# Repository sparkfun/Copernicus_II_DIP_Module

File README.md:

Copernicus II DIP Module
========================

[

[*Copernicus II DIP Module (GPS-11858)*](https://www.sparkfun.com/products/11858)

This breakout board allows access to the SMD pins of the Copernicus II GPS module from Trimble. 

Repository Contents
-------------------
* **/Hardware** - All Eagle design files (.brd, .sch)
* **/Libraries** - All Arduino libraries and board examples
* **/Production** - Test bed files and production panel files

Documentation
-------------------
* **[Hookup Guide](https://learn.sparkfun.com/tutorials/copernicus-ii-hookup-guide)** - Basic hookup guide

Version History
---------------
* [GPS-11067 - v13](https://github.com/sparkfun/Copernicus_II_DIP_Module/tree/79d04dc032e8ecc2a1069bf3677cde6e07c77bf1)

License Information
-------------------
The hardware is released under [Creative Commons Share-alike 3.0](http://creativecommons.org/licenses/by-sa/3.0/). 
All other code is open source so please feel free to do anything you want with it; you buy me a beer if you use this and we meet someday ([Beerware license](http://en.wikipedia.org/wiki/Beerware)).

The library was written by @trbabb. The original repository can be found [here](https://github.com/trbabb/copernicus).

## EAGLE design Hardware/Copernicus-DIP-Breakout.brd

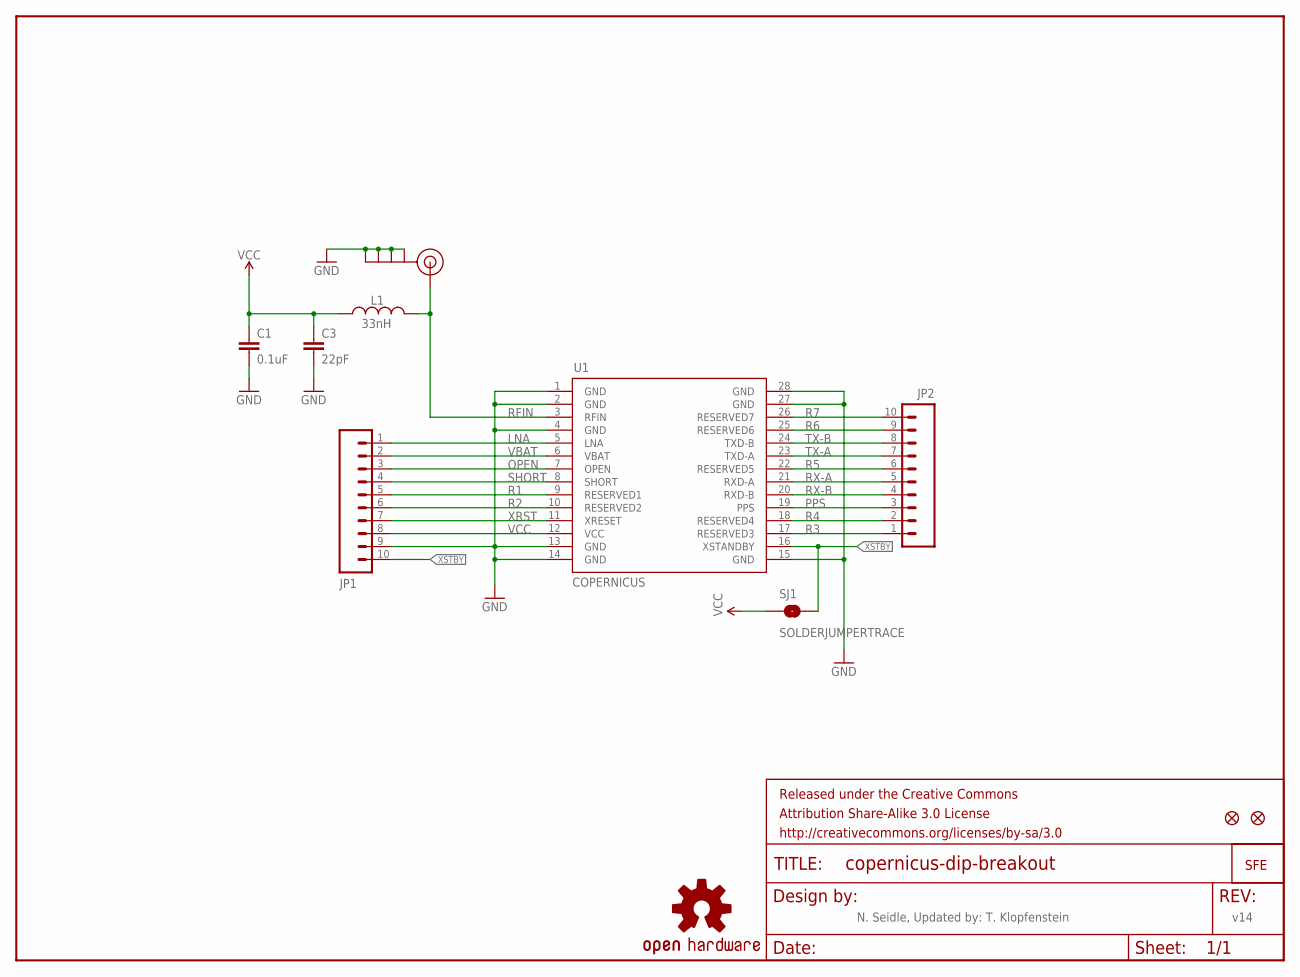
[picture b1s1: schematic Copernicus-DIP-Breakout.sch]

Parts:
C1: 0.1uF; 0603-CAP
C3: 22pF; 0603-CAP
FRAME1: FRAME-LETTER; CREATIVE_COMMONS
JP1, JP2: M10"; 1X10
JP3: SMA_EDGE
JP4: LOGO-SFESK; SFE-LOGO-FLAME
L1: 33nH; 0603
SJ1: SOLDERJUMPERTRACE; SJ_2S-TRACE
U1: COPERNICUS
U$1: OSHW-LOGOS; OSHW-LOGO-S
U$2, U$3: FIDUCIAL1X2; FIDUCIAL-1X2

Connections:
GND: C1.2, C3.2, JP1.9, JP3.GND@0 (GND), JP3.GND@1 (GND), JP3.GND@2 (GND), JP3.GND@3 (GND), U1.1 (GND), U1.2 (GND), U1.4 (GND), U1.13 (GND), U1.14 (GND), U1.15 (GND), U1.27 (GND), U1.28 (GND)
LNA: JP1.1, U1.5 (LNA)
OPEN: JP1.3, U1.7 (OPEN)
PPS: JP2.3, U1.19 (PPS)
R1: JP1.5, U1.9 (RESERVED1)
R2: JP1.6, U1.10 (RESERVED2)
R3: JP2.1, U1.17 (RESERVED3)
R4: JP2.2, U1.18 (RESERVED4)
R5: JP2.6, U1.22 (RESERVED5)
R6: JP2.9, U1.25 (RESERVED6)
R7: JP2.10, U1.26 (RESERVED7)
RFIN: JP3.SIG (SIGNAL), L1.2, U1.3 (RFIN)
RX-A: JP2.5, U1.21 (RXD-A)
RX-B: JP2.4, U1.20 (RXD-B)
SHORT: JP1.4, U1.8 (SHORT)
TX-A: JP2.7, U1.23 (TXD-A)
TX-B: JP2.8, U1.24 (TXD-B)
VBAT: JP1.2, U1.6 (VBAT)
VCC: C1.1, C3.1, JP1.8, L1.1, SJ1.1, U1.12 (VCC)
XRST: JP1.7, U1.11 (XRESET)
XSTBY: JP1.10, SJ1.2, U1.16 (XSTANDBY)

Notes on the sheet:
N. Seidle, Updated by: T. Klopfenstein
v14

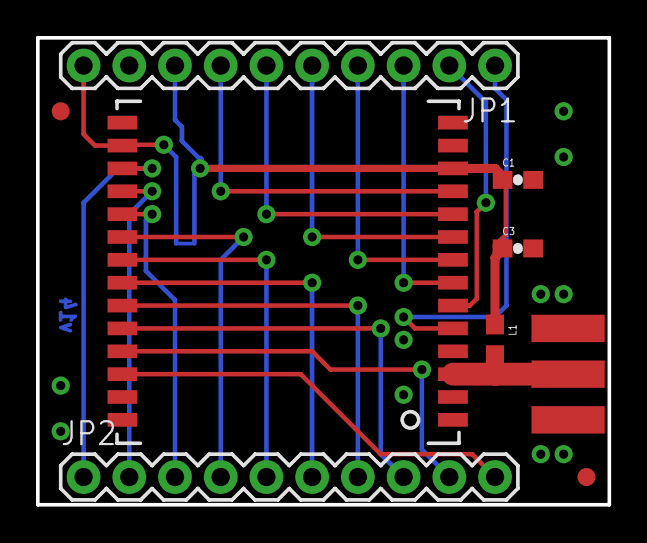
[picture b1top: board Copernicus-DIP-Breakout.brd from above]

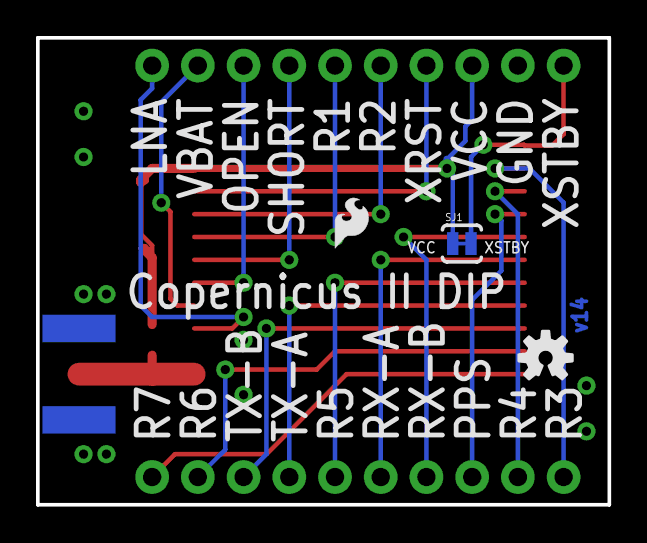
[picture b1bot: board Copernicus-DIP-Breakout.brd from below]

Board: 2 copper layers, 31.8 x 25.9 mm, 13 parts (3 on the bottom side), 21 nets.

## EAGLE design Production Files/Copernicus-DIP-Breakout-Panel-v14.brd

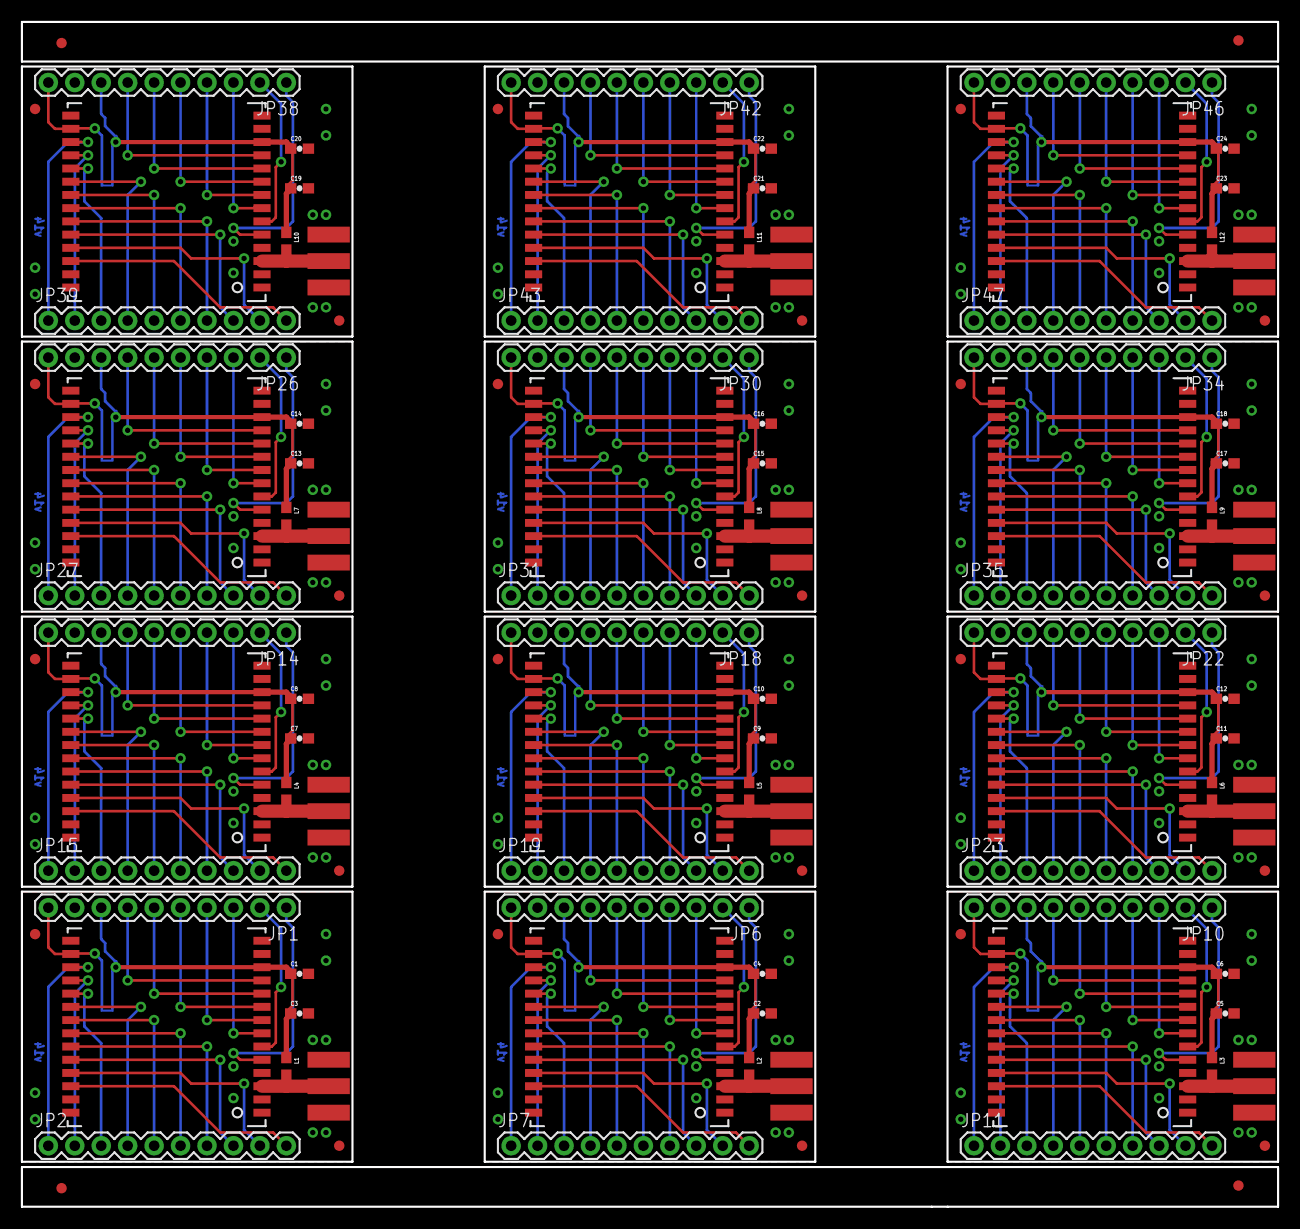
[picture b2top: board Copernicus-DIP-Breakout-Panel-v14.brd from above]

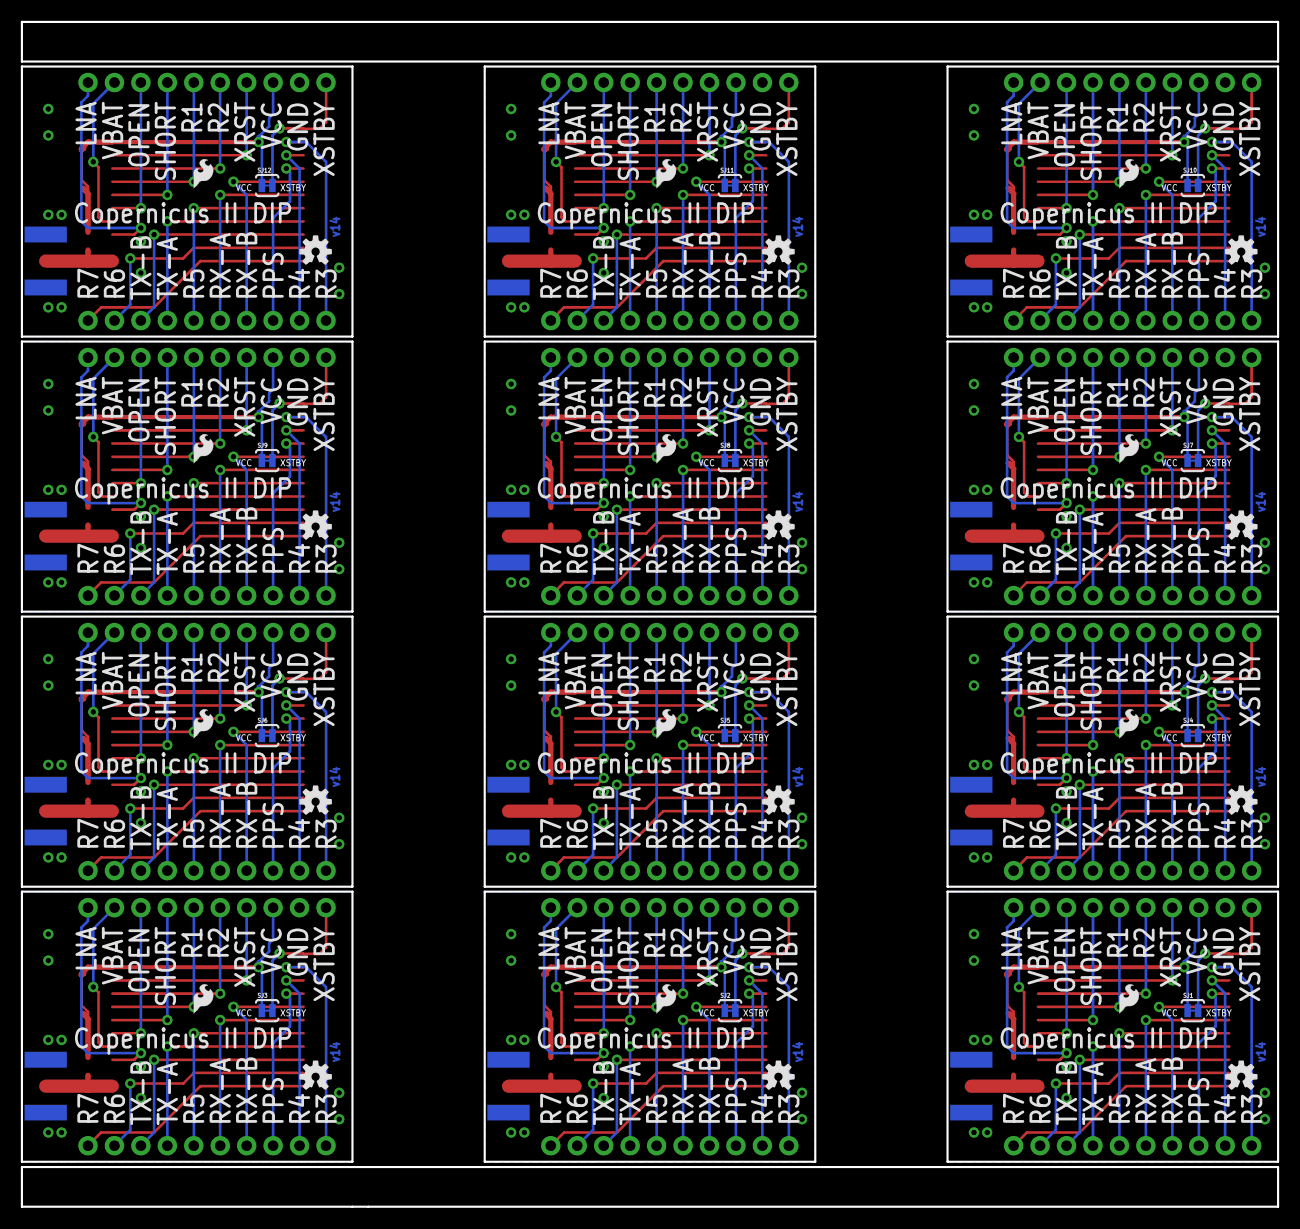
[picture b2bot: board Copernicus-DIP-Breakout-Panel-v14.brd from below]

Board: 2 copper layers, 120.7 x 113.8 mm, 148 parts (36 on the bottom side), 252 nets.

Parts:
C1, C4, C6, C8, C10, C12, C14, C16, C18, C20, C22, C24: 0.1uF; 0603-CAP
C2, C3, C5, C7, C9, C11, C13, C15, C17, C19, C21, C23: 22pF; 0603-CAP
E$1, E$2, E$3, E$4: FIDUCIAL-1X2
JP1, JP2, JP6, JP7, JP10, JP11, JP14, JP15, JP18, JP19, JP22, JP23, JP26, JP27, JP30, JP31, JP34, JP35, JP38, JP39, JP42, JP43, JP46, JP47: 1X10
JP3, JP5, JP9, JP13, JP17, JP21, JP25, JP29, JP33, JP37, JP41, JP45: SMA_EDGE
JP4, JP8, JP12, JP16, JP20, JP24, JP28, JP32, JP36, JP40, JP44, JP48: LOGO-SFESK; SFE-LOGO-FLAME
L1, L2, L3, L4, L5, L6, L7, L8, L9, L10, L11, L12: 33nH; 0603
SJ1, SJ2, SJ3, SJ4, SJ5, SJ6, SJ7, SJ8, SJ9, SJ10, SJ11, SJ12: SOLDERJUMPERTRACE; SJ_2S-TRACE
U1, U2, U3, U4, U5, U6, U7, U8, U9, U10, U11, U12: COPERNICUS
U$1, U$6, U$9, U$12, U$15, U$18, U$21, U$24, U$27, U$30, U$33, U$36: OSHW-LOGOS; OSHW-LOGO-S
U$2, U$3, U$4, U$5, U$7, U$8, U$10, U$11, U$13, U$14, U$16, U$17, U$19, U$20, U$22, U$23, U$25, U$26, U$28, U$29, U$31, U$32, U$34, U$35: FIDUCIAL1X2; FIDUCIAL-1X2

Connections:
GND: C1.2, C3.2, JP1.9, JP3.GND@0, JP3.GND@1, JP3.GND@2, JP3.GND@3, U1.1, U1.2, U1.4, U1.13, U1.14, U1.15, U1.27, U1.28
GND1: C2.2, C4.2, JP5.GND@0, JP5.GND@1, JP5.GND@2, JP5.GND@3, JP6.9, U2.1, U2.2, U2.4, U2.13, U2.14, U2.15, U2.27, U2.28
GND2: C5.2, C6.2, JP9.GND@0, JP9.GND@1, JP9.GND@2, JP9.GND@3, JP10.9, U3.1, U3.2, U3.4, U3.13, U3.14, U3.15, U3.27, U3.28
GND3: C7.2, C8.2, JP13.GND@0, JP13.GND@1, JP13.GND@2, JP13.GND@3, JP14.9, U4.1, U4.2, U4.4, U4.13, U4.14, U4.15, U4.27, U4.28
GND4: C9.2, C10.2, JP17.GND@0, JP17.GND@1, JP17.GND@2, JP17.GND@3, JP18.9, U5.1, U5.2, U5.4, U5.13, U5.14, U5.15, U5.27, U5.28
GND5: C11.2, C12.2, JP21.GND@0, JP21.GND@1, JP21.GND@2, JP21.GND@3, JP22.9, U6.1, U6.2, U6.4, U6.13, U6.14, U6.15, U6.27, U6.28
GND6: C13.2, C14.2, JP25.GND@0, JP25.GND@1, JP25.GND@2, JP25.GND@3, JP26.9, U7.1, U7.2, U7.4, U7.13, U7.14, U7.15, U7.27, U7.28
GND7: C15.2, C16.2, JP29.GND@0, JP29.GND@1, JP29.GND@2, JP29.GND@3, JP30.9, U8.1, U8.2, U8.4, U8.13, U8.14, U8.15, U8.27, U8.28
GND8: C17.2, C18.2, JP33.GND@0, JP33.GND@1, JP33.GND@2, JP33.GND@3, JP34.9, U9.1, U9.2, U9.4, U9.13, U9.14, U9.15, U9.27, U9.28
GND9: C19.2, C20.2, JP37.GND@0, JP37.GND@1, JP37.GND@2, JP37.GND@3, JP38.9, U10.1, U10.2, U10.4, U10.13, U10.14, U10.15, U10.27, U10.28
GND10: C21.2, C22.2, JP41.GND@0, JP41.GND@1, JP41.GND@2, JP41.GND@3, JP42.9, U11.1, U11.2, U11.4, U11.13, U11.14, U11.15, U11.27, U11.28
GND11: C23.2, C24.2, JP45.GND@0, JP45.GND@1, JP45.GND@2, JP45.GND@3, JP46.9, U12.1, U12.2, U12.4, U12.13, U12.14, U12.15, U12.27, U12.28
LNA: JP1.1, U1.5
LNA1: JP6.1, U2.5
LNA2: JP10.1, U3.5
LNA3: JP14.1, U4.5
LNA4: JP18.1, U5.5
LNA5: JP22.1, U6.5
LNA6: JP26.1, U7.5
LNA7: JP30.1, U8.5
LNA8: JP34.1, U9.5
LNA9: JP38.1, U10.5
LNA10: JP42.1, U11.5
LNA11: JP46.1, U12.5
OPEN: JP1.3, U1.7
OPEN1: JP6.3, U2.7
OPEN2: JP10.3, U3.7
OPEN3: JP14.3, U4.7
OPEN4: JP18.3, U5.7
OPEN5: JP22.3, U6.7
OPEN6: JP26.3, U7.7
OPEN7: JP30.3, U8.7
OPEN8: JP34.3, U9.7
OPEN9: JP38.3, U10.7
OPEN10: JP42.3, U11.7
OPEN11: JP46.3, U12.7
PPS: JP2.3, U1.19
PPS1: JP7.3, U2.19
PPS2: JP11.3, U3.19
PPS3: JP15.3, U4.19
PPS4: JP19.3, U5.19
PPS5: JP23.3, U6.19
PPS6: JP27.3, U7.19
PPS7: JP31.3, U8.19
PPS8: JP35.3, U9.19
PPS9: JP39.3, U10.19
PPS10: JP43.3, U11.19
PPS11: JP47.3, U12.19
R1: JP1.5, U1.9
R2: JP1.6, U1.10
R3: JP2.1, U1.17
R4: JP2.2, U1.18
R5: JP2.6, U1.22
R6: JP2.9, U1.25
R7: JP2.10, U1.26
R8: JP6.5, U2.9
R9: JP6.6, U2.10
R10: JP7.10, U2.26
R11: JP7.9, U2.25
R12: JP7.6, U2.22
R13: JP7.2, U2.18
R14: JP7.1, U2.17
R15: JP10.5, U3.9
R16: JP10.6, U3.10
R17: JP11.10, U3.26
R18: JP11.9, U3.25
R19: JP11.6, U3.22
R20: JP11.2, U3.18
R21: JP11.1, U3.17
R22: JP14.5, U4.9
R23: JP14.6, U4.10
R24: JP15.10, U4.26
R25: JP15.9, U4.25
R26: JP15.6, U4.22
R27: JP15.2, U4.18
R28: JP15.1, U4.17
R29: JP18.5, U5.9
R30: JP18.6, U5.10
R31: JP19.10, U5.26
R32: JP19.9, U5.25
R33: JP19.6, U5.22
R34: JP19.2, U5.18
R35: JP19.1, U5.17
R36: JP22.5, U6.9
R37: JP22.6, U6.10
R38: JP23.10, U6.26
R39: JP23.9, U6.25
R40: JP23.6, U6.22
R41: JP23.2, U6.18
R42: JP23.1, U6.17
R43: JP26.5, U7.9
R44: JP26.6, U7.10
R45: JP27.10, U7.26
R46: JP27.9, U7.25
R47: JP27.6, U7.22
R48: JP27.2, U7.18
R49: JP27.1, U7.17
R50: JP30.5, U8.9
R51: JP30.6, U8.10
R52: JP31.10, U8.26
R53: JP31.9, U8.25
R54: JP31.6, U8.22
R55: JP31.2, U8.18
R56: JP31.1, U8.17
R57: JP34.5, U9.9
R58: JP34.6, U9.10
R59: JP35.10, U9.26
R60: JP35.9, U9.25
R61: JP35.6, U9.22
R62: JP35.2, U9.18
R63: JP35.1, U9.17
R64: JP38.5, U10.9
R65: JP38.6, U10.10
R66: JP39.10, U10.26
R67: JP39.9, U10.25
R68: JP39.6, U10.22
R69: JP39.2, U10.18
R70: JP39.1, U10.17
R71: JP42.5, U11.9
R72: JP42.6, U11.10
R73: JP43.10, U11.26
R74: JP43.9, U11.25
R75: JP43.6, U11.22
R76: JP43.2, U11.18
R77: JP43.1, U11.17
R78: JP46.5, U12.9
R79: JP46.6, U12.10
R80: JP47.10, U12.26
R81: JP47.9, U12.25
R82: JP47.6, U12.22
R83: JP47.2, U12.18
R84: JP47.1, U12.17
RFIN: JP3.SIG, L1.2, U1.3
RFIN1: JP5.SIG, L2.2, U2.3
RFIN2: JP9.SIG, L3.2, U3.3
RFIN3: JP13.SIG, L4.2, U4.3
RFIN4: JP17.SIG, L5.2, U5.3
RFIN5: JP21.SIG, L6.2, U6.3
RFIN6: JP25.SIG, L7.2, U7.3
RFIN7: JP29.SIG, L8.2, U8.3
RFIN8: JP33.SIG, L9.2, U9.3
RFIN9: JP37.SIG, L10.2, U10.3
RFIN10: JP41.SIG, L11.2, U11.3
RFIN11: JP45.SIG, L12.2, U12.3
RX-A: JP2.5, U1.21
RX-A1: JP7.5, U2.21
RX-A2: JP11.5, U3.21
RX-A3: JP15.5, U4.21
RX-A4: JP19.5, U5.21
RX-A5: JP23.5, U6.21
RX-A6: JP27.5, U7.21
RX-A7: JP31.5, U8.21
RX-A8: JP35.5, U9.21
RX-A9: JP39.5, U10.21
RX-A10: JP43.5, U11.21
RX-A11: JP47.5, U12.21
RX-B: JP2.4, U1.20
RX-B1: JP7.4, U2.20
RX-B2: JP11.4, U3.20
RX-B3: JP15.4, U4.20
RX-B4: JP19.4, U5.20
RX-B5: JP23.4, U6.20
RX-B6: JP27.4, U7.20
RX-B7: JP31.4, U8.20
RX-B8: JP35.4, U9.20
RX-B9: JP39.4, U10.20
RX-B10: JP43.4, U11.20
RX-B11: JP47.4, U12.20
SHORT: JP1.4, U1.8
SHORT1: JP6.4, U2.8
SHORT2: JP10.4, U3.8
SHORT3: JP14.4, U4.8
SHORT4: JP18.4, U5.8
SHORT5: JP22.4, U6.8
SHORT6: JP26.4, U7.8
SHORT7: JP30.4, U8.8
SHORT8: JP34.4, U9.8
SHORT9: JP38.4, U10.8
SHORT10: JP42.4, U11.8
SHORT11: JP46.4, U12.8
TX-A: JP2.7, U1.23
TX-A1: JP7.7, U2.23
TX-A2: JP11.7, U3.23
TX-A3: JP15.7, U4.23
TX-A4: JP19.7, U5.23
TX-A5: JP23.7, U6.23
TX-A6: JP27.7, U7.23
TX-A7: JP31.7, U8.23
TX-A8: JP35.7, U9.23
TX-A9: JP39.7, U10.23
TX-A10: JP43.7, U11.23
TX-A11: JP47.7, U12.23
TX-B: JP2.8, U1.24
TX-B1: JP7.8, U2.24
TX-B2: JP11.8, U3.24
TX-B3: JP15.8, U4.24
TX-B4: JP19.8, U5.24
TX-B5: JP23.8, U6.24
TX-B6: JP27.8, U7.24
TX-B7: JP31.8, U8.24
TX-B8: JP35.8, U9.24
TX-B9: JP39.8, U10.24
TX-B10: JP43.8, U11.24
TX-B11: JP47.8, U12.24
VBAT: JP1.2, U1.6
VBAT1: JP6.2, U2.6
VBAT2: JP10.2, U3.6
VBAT3: JP14.2, U4.6
VBAT4: JP18.2, U5.6
VBAT5: JP22.2, U6.6
VBAT6: JP26.2, U7.6
VBAT7: JP30.2, U8.6
VBAT8: JP34.2, U9.6
VBAT9: JP38.2, U10.6
VBAT10: JP42.2, U11.6
VBAT11: JP46.2, U12.6
VCC: C1.1, C3.1, JP1.8, L1.1, SJ1.1, U1.12
VCC1: C2.1, C4.1, JP6.8, L2.1, SJ2.1, U2.12
VCC2: C5.1, C6.1, JP10.8, L3.1, SJ3.1, U3.12
VCC3: C7.1, C8.1, JP14.8, L4.1, SJ4.1, U4.12
VCC4: C9.1, C10.1, JP18.8, L5.1, SJ5.1, U5.12
VCC5: C11.1, C12.1, JP22.8, L6.1, SJ6.1, U6.12
VCC6: C13.1, C14.1, JP26.8, L7.1, SJ7.1, U7.12
VCC7: C15.1, C16.1, JP30.8, L8.1, SJ8.1, U8.12
VCC8: C17.1, C18.1, JP34.8, L9.1, SJ9.1, U9.12
VCC9: C19.1, C20.1, JP38.8, L10.1, SJ10.1, U10.12
VCC10: C21.1, C22.1, JP42.8, L11.1, SJ11.1, U11.12
VCC11: C23.1, C24.1, JP46.8, L12.1, SJ12.1, U12.12
XRST: JP1.7, U1.11
XRST1: JP6.7, U2.11
XRST2: JP10.7, U3.11
XRST3: JP14.7, U4.11
XRST4: JP18.7, U5.11
XRST5: JP22.7, U6.11
XRST6: JP26.7, U7.11
XRST7: JP30.7, U8.11
XRST8: JP34.7, U9.11
XRST9: JP38.7, U10.11
XRST10: JP42.7, U11.11
XRST11: JP46.7, U12.11
XSTBY: JP1.10, SJ1.2, U1.16
XSTBY1: JP6.10, SJ2.2, U2.16
XSTBY2: JP10.10, SJ3.2, U3.16
XSTBY3: JP14.10, SJ4.2, U4.16
XSTBY4: JP18.10, SJ5.2, U5.16
XSTBY5: JP22.10, SJ6.2, U6.16
XSTBY6: JP26.10, SJ7.2, U7.16
XSTBY7: JP30.10, SJ8.2, U8.16
XSTBY8: JP34.10, SJ9.2, U9.16
XSTBY9: JP38.10, SJ10.2, U10.16
XSTBY10: JP42.10, SJ11.2, U11.16
XSTBY11: JP46.10, SJ12.2, U12.16

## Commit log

2013-05-06 Initial commit of board files.
2013-05-06 Update Hardware file
2013-05-06 Fix silk screen on board file
2013-05-14 Updated board to proper pin names, added in connection between XSTBY and Vcc, changed caps and inductor to 0603 package, and decreased PCB size.
2013-06-03 Fixing version number and solder jumper silkscreen.
2013-06-06 v14 Readied for production
    created panel
2013-10-08 Updating README
2013-10-08 Additional README changes
2014-01-28 Adding Copernicus Library to repo
2025-06-27 Update README.md
    Updating link

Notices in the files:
parts and their libraries:
SparkFun-RF: Licensing: CC v3.0 Share-Alike You are welcome to use this library for commercial purposes.
SparkFun-Aesthetics: Released under the Creative Commons Attribution Share-Alike 3.0 License
SparkFun-Aesthetics: Released under the Creative Commons
